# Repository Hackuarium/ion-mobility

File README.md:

# What is Ion Mobility Spectrometry ?

[https://en.wikipedia.org/wiki/Ion-mobility_spectrometry]

# Why should we do this ?

There are numerous application for IMS and it has the main advantage to work at atmospheric pressure (in constraste with mass spectrometry that requires most of the time 10-3 torr) that would make it compact and affordable.

We see the possibility to make continious monitoring of the bioreactor made by Hackuarium and situated in Cali, Colombia.

# Can we do a Ion Mobility Spectrometer our self ?

Main parts of the IMS :

- Desolvation zone : Insert and ionization of sample. 
Electrospray ionisation (ESI). Advantage : one can insert the liquid sample and ionize it through the same needle. 
Limitation : 5kV voltage source, 100uL/min flow rate through the needle. 

- Shutter : Let the ions pass on command.
Three grid Shutter. Advantage : easy to built and to command. 

- Drift zone : Acceleration of ions.
Made by multiple electrodes connected to different voltages with the aid of a voltage divider. 
Limitation : 10kV voltage source. 

- Detection : Faraday plate.
Transconductance amplifier converts the tiny ion current into a reasonable tension.
Limitation : The current-to-tension AOP must be with very low bias current, and low noise (hence expensive). 

- Monitoring : A/D converter. 

Link to full project already made : [https://github.com/bhclowers/OS-IMS]

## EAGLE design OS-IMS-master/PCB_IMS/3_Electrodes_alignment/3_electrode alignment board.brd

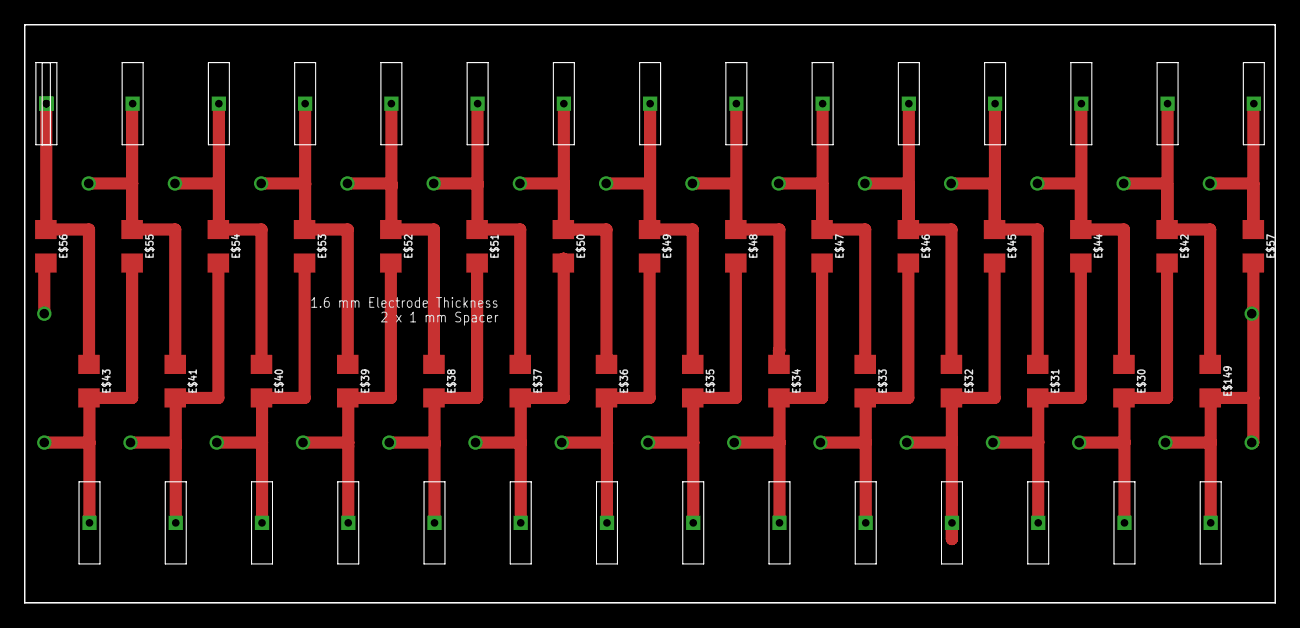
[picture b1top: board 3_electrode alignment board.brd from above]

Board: 2 copper layers, 104.4 x 48.3 mm, 59 parts (0 on the bottom side), 3 nets.

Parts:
E$1, E$2, E$3, E$4, E$5, E$6, E$7, E$8, E$9, E$10, E$11, E$12, E$13, E$14, E$15, E$16, E$17, E$18, E$19, E$20, E$21, E$22, E$23, E$24, E$25, E$26, E$27, E$28, E$29: SLOT2
E$30, E$31, E$32, E$33, E$34, E$35, E$36, E$37, E$38, E$39, E$40, E$41, E$42, E$43, E$44, E$45, E$46, E$47, E$48, E$49, E$50, E$51, E$52, E$53, E$54, E$55, E$56, E$57, E$149: 1206
E$222: SLOT1

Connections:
S$1: E$43.1, E$56.1, E$222.P$1
S$11: E$2.P$1, E$16.P$1, E$17.P$1, E$18.P$1, E$19.P$1, E$20.P$1, E$21.P$1, E$22.P$1, E$23.P$1, E$24.P$1, E$25.P$1, E$26.P$1, E$27.P$1, E$28.P$1, E$30.2, E$31.2, E$32.2, E$33.2, E$34.2, E$35.2, E$36.2, E$37.2, E$38.2, E$39.2, E$40.2, E$41.2, E$42.2, E$43.2, E$44.2, E$45.2, E$46.2, E$47.2, E$48.2, E$49.2, E$50.2, E$51.2, E$52.2, E$53.2, E$54.2, E$55.2, E$57.2, E$149.2
S$12: E$3.P$1, E$4.P$1, E$5.P$1, E$6.P$1, E$7.P$1, E$8.P$1, E$9.P$1, E$10.P$1, E$11.P$1, E$12.P$1, E$13.P$1, E$14.P$1, E$15.P$1, E$29.P$1, E$30.1, E$31.1, E$32.1, E$33.1, E$34.1, E$35.1, E$36.1, E$37.1, E$38.1, E$39.1, E$40.1, E$41.1, E$42.1, E$44.1, E$45.1, E$46.1, E$47.1, E$48.1, E$49.1, E$50.1, E$51.1, E$52.1, E$53.1, E$54.1, E$55.1, E$57.1, E$149.1

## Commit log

2019-10-05 Rename Shutter_info.txt to Shutter_info.md
2019-10-06 Create Ionization_info
2019-10-06 Rename Ionization_info to Ionization_info.md
2019-10-06 Add files via upload
    Electrospray
2019-10-16 Create Additionnal stuff
2019-11-30 add pcb from publication
2019-12-01 add gitignore
2019-12-01 chore: update boards on pcbway requests
2020-03-05 test_changement_de_nom
2020-03-05 ajout du catia
2020-03-05 refactorm
2020-03-05 test_change
2020-03-05 fin_test
2020-03-05 PCB for voltage divider
2020-03-05 reorganisation
2020-03-05 modif of schematics
2020-03-06 Change name
2020-03-06 Moved parts
2020-03-06 tracks realised
2020-03-06 Dimensions of pcb
    Power parts brought together, and length of pcb smaller
2020-03-06 Power tracks enlarged
2020-03-06 Signal tracks enlarged
2020-03-06 Footprint changes
2020-03-06 Begin PCB of divider
2020-03-06 divider
2020-03-07 Pbs with footprints
2020-03-07 PCB + new electrodes
2020-03-07 1st pcb done
2020-03-07 added tips about low noise pcb design
2020-03-08 catia update
2020-03-08 Divider1: Without tracks
2020-03-08 Reorganize
2020-03-08 Dividers finished without testing points
2020-03-08 Divider finished with test points
2020-03-08 Most parts completed
2020-03-09 low noise pcb design
2020-03-10 Small corrections
2020-03-10 Revert "Small corrections"
2020-03-10 Low noise smd amp
2020-03-10 SMD + low noise design
2020-03-11 low noise features
2020-03-11 Small mistakes
2020-03-11 pcd target added
2020-03-21 GND guards are neat!
2020-03-22 Implementation of the HV sources footprints and schems
2020-03-24 Small modifications
2020-03-25 Implementing MCU
2020-03-25 Labelling/ordering stuff
2020-04-07 Small modif
2020-04-08 DC/DC isolated converter implementation
2020-04-09 Set a Vin of 5V
2020-04-09 Small changes
2020-04-09 Implementation of ESP32 code
2020-04-09 New version of code
2020-04-11 Simplification of the functions
2020-04-17 New isolated alimentation design
2020-04-29 Modifications of the amplification part
2020-06-01 Voltage measure circuits
2020-06-02 Begin PCB design
2020-06-02 Components in place
2020-06-05 Electrode design
2020-06-05 HV design finished
2020-06-08 Improve PCBs
2020-06-08 code update: final file is in test4
2020-06-11 Ampli last version - low noise guarding
2020-06-11 Alim&control update
2020-06-12 Updates of dividers 1 & 2
2020-07-13 Complete divider update
2023-06-01 Create README for ampli
2023-06-01 Add README files
2023-06-01 Add new CAD files version V2
    New CAD files for version V2 of 3D printed IMS. New folders created to reorganize CAD files in efficient way.
2023-06-02 Update README.md
    Bug correction
2023-06-02 Update README.md
    readme CAD V2
2023-06-03 Nafion specification
2023-06-05 add pictures in README.md
2023-06-05 Update README.md ampli
2023-06-08 Add V3 IMS CAD version
2023-06-09 README update
2023-06-09 Ajout readme

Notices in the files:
parts and their libraries:
SparkFun-Resistors: Licensing: Creative Commons ShareAlike 4.0 International - https://creativecommons.org/licenses/by-sa/4.0
